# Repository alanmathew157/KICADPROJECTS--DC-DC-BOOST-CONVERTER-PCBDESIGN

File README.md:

# DC-DC-BOOST CONVERTER PCB Design using KICAD -ALTIMUM
## PCB TOP VIEW

## PCB BOTTOM VIEW

## Project Overview🔧
This schematic represents a DC-DC boost converter designed as part of my learning process in PCB design using KiCad. The circuit works by stepping up a lower DC input voltage to a higher output voltage using the basic principle of energy storage and switching. When the switching element (typically a transistor or switching IC) turns ON, current flows through the inductor and energy is stored in its magnetic field. When the switch turns OFF, the inductor releases this stored energy, causing the voltage across it to rise. This higher voltage is then directed through a diode to the output capacitor, which smooths the voltage and supplies a stable DC output to the load. The capacitor also helps reduce ripple in the output voltage, while resistors in the circuit help regulate feedback and control the switching behavior. By repeatedly switching at high frequency, the circuit effectively boosts the input voltage to a higher level. Designing this schematic helped me understand both the working principle of boost converters and the practical aspects of schematic creation and PCB design using KiCad.

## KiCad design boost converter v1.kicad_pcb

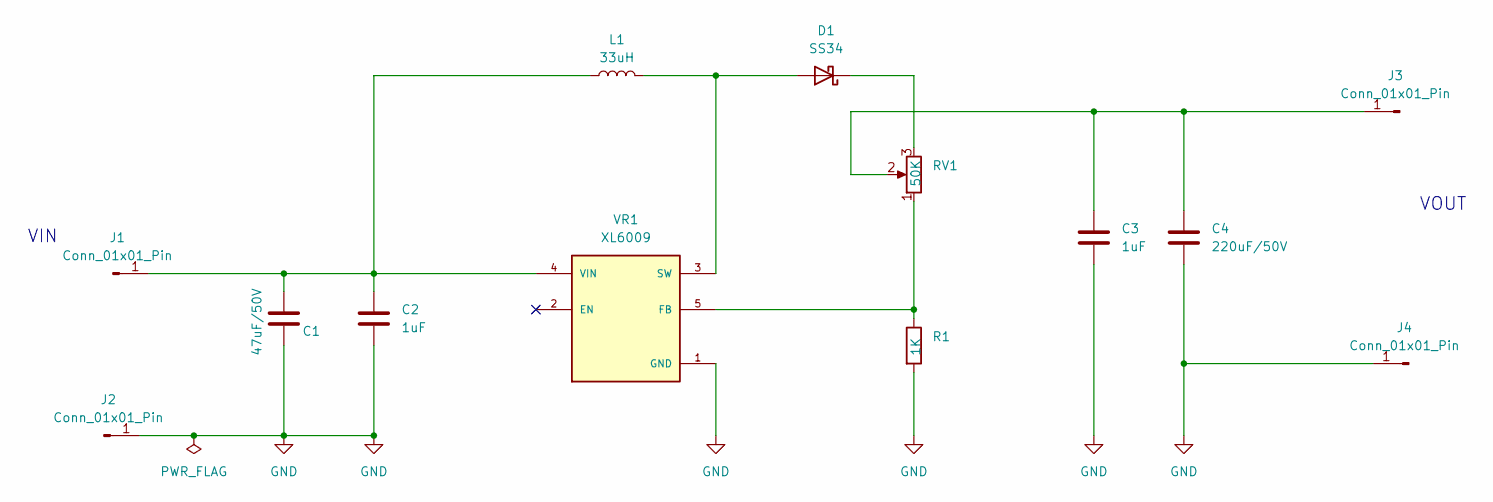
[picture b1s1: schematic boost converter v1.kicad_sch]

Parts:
C1: 47uF/50V; CP_Radial_D6.3mm_P2.50mm
C2, C3: 1uF; C_0805_2012Metric
C4: 220uF/50V; CP_Radial_D6.3mm_P2.50mm
D1: SS34; D_SMA
J1, J2, J3, J4: Conn_01x01_Pin; PinHeader_1x01_P2.54mm_Vertical
L1: 33uH; L_12x12mm_H8mm
R1: 1K; R_1206_3216Metric
RV1: 50K; Potentiometer_Bourns_3296W_Vertical
VR1: XL6009; DPAK170P1435X465-6N; PARTREV 1.1

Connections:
GND: C1.2, C2.2, C3.2, C4.2, J2.1, J4.1, R1.2, VR1.1 (GND)
unnamed: D1.2 (A), L1.2, VR1.3 (SW), VR1.6 (SW)
unnamed: D1.1 (K), RV1.3
unnamed: C1.1, C2.1, J1.1, L1.1, VR1.4 (VIN)
unnamed: C3.1, C4.1, J3.1, RV1.2
unnamed: R1.1, RV1.1, VR1.5 (FB)

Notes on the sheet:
VOUT
VIN

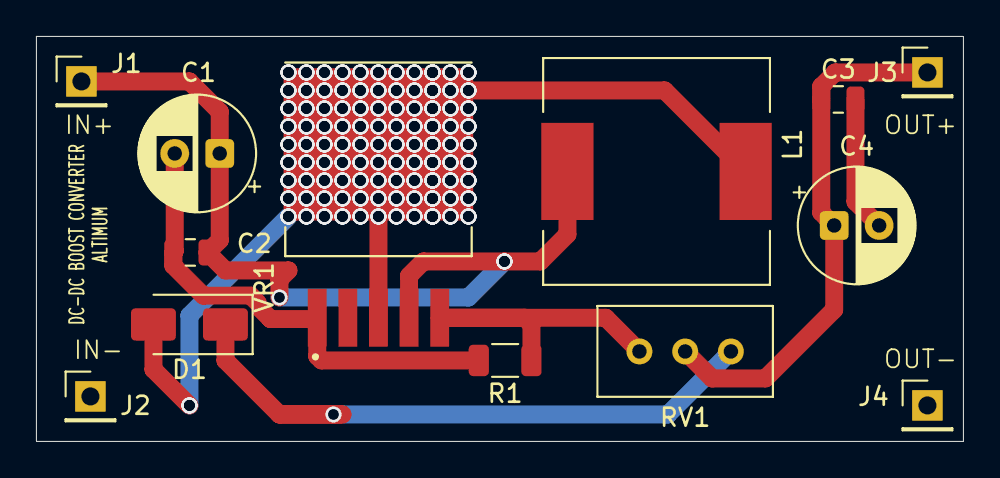
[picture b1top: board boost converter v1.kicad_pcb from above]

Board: 2 copper layers, 51.5 x 22.5 mm, 13 parts (0 on the bottom side), 6 nets.
